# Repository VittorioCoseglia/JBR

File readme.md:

# JBR 

**JBR** es un parlante amplificado estéreo de diseño abierto. Combina dos etapas de potencia **clase AB** de 12 W sobre 8 Ω, una fuente lineal simétrica y un receptor **Bluetooth 5.0** (módulo [VHM‑314](docs/datasheet/VHM-314.pdf)), todo dentro de un gabinete impreso en 3D.

El repositorio reúne el diseño completo en **KiCad 9**, los planos de fabricación, el modelo 3D del gabinete, la simulación en **[Multisim](docs/markdown/simulation.md)** y el manual de usuario. Está pensado como proyecto educativo y como base reutilizable para otros amplificadores.

> [!WARNING]
> El equipo funciona con **220 V AC**. El interior del gabinete tiene tensiones peligrosas: no lo abras ni lo manipules conectado a la red. Las reparaciones y el primer encendido deben realizarse por un técnico.

## Contenido

- [Características](#características)
- [Arquitectura](#arquitectura)
- [Placas](#placas)
- [Estructura del repositorio](#estructura-del-repositorio)
- [Puesta en marcha](#puesta-en-marcha)
- [Fabricación](#fabricación)
- [Seguridad](#seguridad)
- [Créditos y contacto](#créditos-y-contacto)

## Características

| Característica | Valor |
|---|---|
| Configuración | Estéreo, 2 canales (2 placas AB) |
| Potencia | **2 × 12 W RMS @ 8 Ω**|
| Rieles de alimentación | ≈ ±16 VDC nominales (transformador 12‑0‑12 VAC) |
| Alimentación | 220 V AC, 50/60 Hz |
| Bluetooth | 5.0, módulo **[VHM‑314](docs/datasheet/VHM-314.pdf)** |
| Gabinete | 270 × 140 × 135 mm |
| Herramientas | KiCad 9.0, SolidWorks 2022, AutoCAD, Multisim 14 |

## Arquitectura

```mermaid
flowchart LR
    AC["220 V AC"] --> PSU["±12 V AC<br/>Fuente ±16 VDC"]
    PSU -->|"+VDC / GND / -VDC"| AMP_L["AB<br/>canal izquierdo"]
    PSU -->|"+VDC / GND / -VDC"| AMP_R["AB<br/>canal derecho"]
    PSU -->|"VCC / GND"| BT["VHM-314<br/>Bluetooth 5.0"]
    BT -->|"audio L"| AMP_L
    BT -->|"audio R"| AMP_R
    AMP_L --> SPK_L["Parlante 8 Ω"]
    AMP_R --> SPK_R["Parlante 8 Ω"]
```

La fuente entrega tres salidas ±VDC: dos se usan para las etapas de potencia y una para el control. El módulo Bluetooth entrega las señales de audio izquierda y derecha a cada amplificador.

## Placas

| Placa | Función | Documentación | Esquemático |
|---|---|---|---|
| **AB** | Etapa de potencia clase AB, 12 W / 8 Ω (una por canal) | [AB](docs/markdown/ab.md) | [ABSchem](docs/PDF/Schem/ABSchem.pdf) |
| **Fuente x4** | Fuente simétrica ±16 VDC con tres salidas | [Fuente](docs/markdown/fuente.md) | [FuenteSchem](docs/PDF/Schem/FuenteSchem.pdf) |
| **Control** | Regulador 5 V, LED y conexión del módulo Bluetooth | [Control](docs/markdown/control.md) | [ControlSchem](docs/PDF/Schem/ControlSchem.pdf) |

También están disponibles las [transferencias para fabricación](docs/PDF/Transferencia), los [datasheets](docs/datasheet) y la [lista de materiales](docs/BOM.xlsx). El esquemático del amplificador está en [ABSchem](docs/PDF/Schem/ABSchem.pdf).

## Estructura del repositorio

```text
.
├── AB/                    # Proyecto KiCad de la etapa de potencia
├── Control/                  # Proyecto KiCad del control y Bluetooth
├── Fuente/                   # Proyecto KiCad de la fuente simétrica
├── gabinete/                 # Ensamble SolidWorks, STL para impresión 3D y STEP
├── Manual/                   # Manual de usuario en Word, fotos y video
├── Simulacion/               # Simulación del amplificador en Multisim
├── docs/
│   ├── BOM.xlsx              # Lista de materiales completa
│   ├── datasheet/            # Hojas de datos de los componentes principales
│   ├── img/                  # Fotos e imágenes de las placas y del equipo
│   ├── PDF/                  # Esquemáticos (Schem/) y transferencias por placa
│   └── markdown/             # Documentación técnica de cada placa
└── readme.md
```

## Puesta en marcha

1. **Revisar la fuente antes de conectar las placas.** Con el transformador conectado y sin carga, medir ±VDC entre cada riel y GND. Verificar también que no haya tensión AC en las salidas.
2. **Ajustar el bias de cada AB** con el amplificador sin señal y con la placa a temperatura de trabajo. Medir la caída sobre `R8` y `R9` (0,33 Ω) y ajustar `RV2` hasta obtener aproximadamente **10–15 mV** en cada resistencia (≈ 30–45 mA por par de salida). Ver [AB](docs/markdown/ab.md#ajustes).
3. **Ajustar la ganancia** con `RV1` (100 kΩ). Para una entrada típica de 1 V RMS, un valor cercano a 12 kΩ entrega la ganancia necesaria para la potencia nominal.
4. **Conectar el control** a una salida de la fuente y verificar los 5 V en la salida del [L7805](docs/datasheet/L7805.pdf) antes de colocar el módulo [VHM‑314](docs/datasheet/VHM-314.pdf).
5. **Vincular el Bluetooth**: encender el equipo y buscar el dispositivo **HFW-BT** desde el celular.

## Fabricación

- **Placas:** 100 × 50 mm, 2 capas, componentes de agujero pasante (THT). Los PDF de transferencia están en [`docs/PDF/Transferencia/`](docs/PDF/Transferencia).
- **Componentes:** la [BOM](docs/BOM.xlsx) está separada por placa ([fuente](docs/markdown/fuente.md), [AB](docs/markdown/ab.md), [control](docs/markdown/control.md), [gabinete](docs/markdown/case.md) y [accesorios](docs/markdown/case.md)). La BOM del AB corresponde a **un canal**; para el equipo estéreo hay que duplicarla.
- **Disipadores:** los [TIP31C](docs/datasheet/TIP31C.pdf)/[TIP32C](docs/datasheet/TIP32C.pdf) van sobre disipador TO‑220 y los [BD139](docs/datasheet/BD13X.pdf)/[BD140](docs/datasheet/BD13X.pdf) sobre disipador TO‑126. Usar grasa térmica y aislantes si el disipador queda unido al chasis.
- **[gabinete](docs/markdown/case.md):** piezas `abajo.STL` y `arriba.STL` en `gabinete/Impresion 3D/stl/` para impresión 3D, más el ensamble SolidWorks y las piezas STEP de las placas.
## Seguridad

- Conectar únicamente a **220 V AC, 50/60 Hz** con el cable C13 incluido.
- No abrir el gabinete con el equipo conectado. Los capacitores de la fuente pueden quedar cargados después de apagarlo: descargarlos con una resistencia antes de manipular.
- No cubrir el equipo ni apoyarlo sobre superficies blandas; los disipadores y el transformador se calientan.
- Evitar el uso prolongado a volumen máximo o con sonido distorsionado.
- Mantener lejos del agua y fuera del alcance de los niños.
- Reemplazar el fusible solo por otro del mismo tipo y valor, con el equipo **desconectado de la red**.

## Créditos y contacto

- **Autor:** Vittorio Coseglia
- **Repositorio:** [github.com/VittorioCoseglia/JBR](https://github.com/VittorioCoseglia/JBR)
- **Consultas y errores:** [abrir un issue](https://github.com/VittorioCoseglia/JBR/issues)
- **Correo:** vittorio.coseglia@gmail.com

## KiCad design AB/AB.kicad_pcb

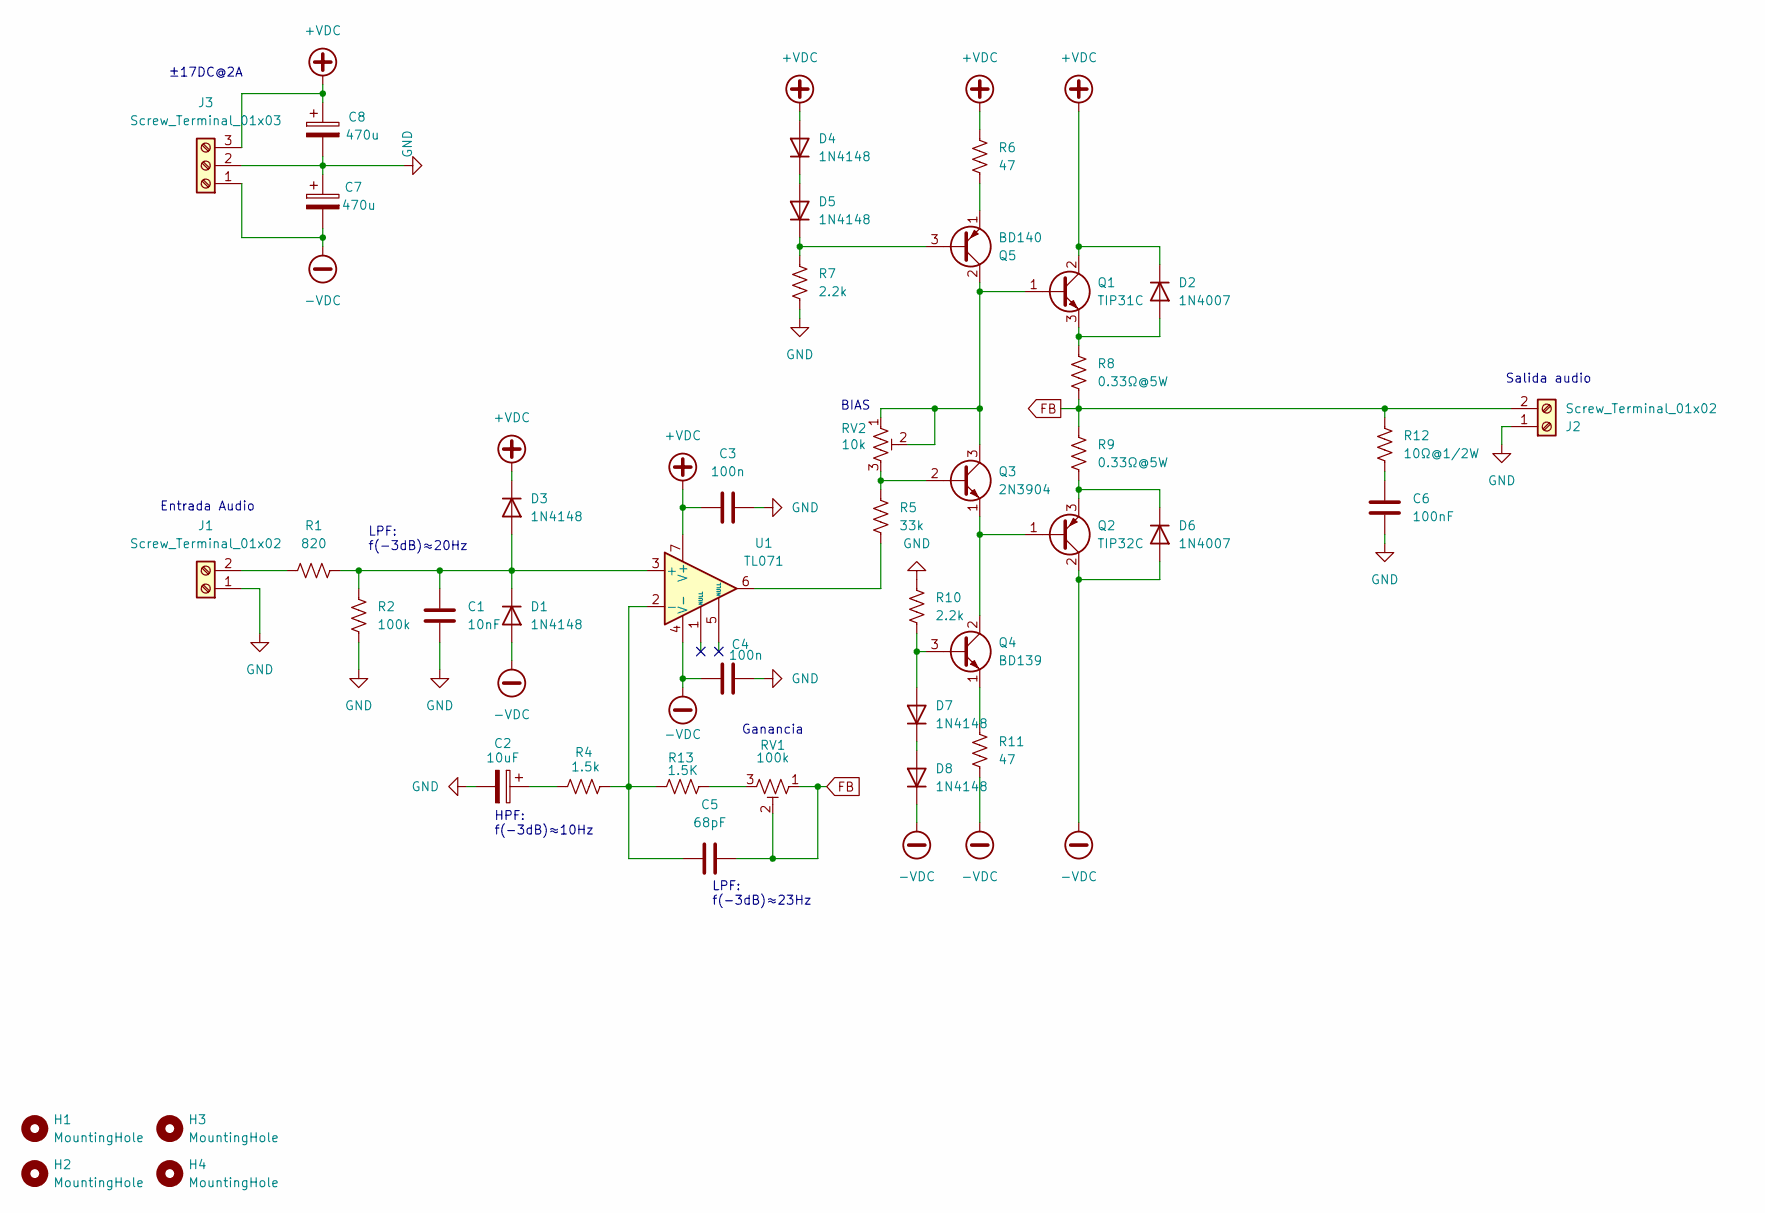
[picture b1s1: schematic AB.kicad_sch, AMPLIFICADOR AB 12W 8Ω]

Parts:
C1: 10nF; C_Disc_D5.0mm_W2.5mm_P2.50mm
C2: 10uF; C_Radial_D6.3mm_H11.0mm_P2.50mm
C3, C4: 100n; C_Disc_D5.0mm_W2.5mm_P2.50mm
C5: 68pF; C_Disc_D3.0mm_W2.0mm_P2.50mm
C6: 100nF; C_Disc_D5.0mm_W2.5mm_P2.50mm
C7, C8: 470u; C_Radial_D10.0mm_H20.0mm_P5.00mm
D1, D3, D4, D5, D7, D8: 1N4148; D_DO-35_SOD27_P7.62mm_Horizontal
D2, D6: 1N4007; D_DO-41_SOD81_P10.16mm_Horizontal
H1, H2, H3, H4: MountingHole; MountingHole_3.2mm_M3
J1, J2: Screw_Terminal_01x02; TerminalBlock_Phoenix_MKDS-1,5-2_1x02_P5.00mm_Horizontal
J3: Screw_Terminal_01x03; TerminalBlock_Phoenix_MKDS-1,5-3_1x03_P5.00mm_Horizontal
Q1: TIP31C; TO-220-3_Vertical
Q2: TIP32C; TO-220-3_Vertical
Q3: 2N3904; TO-92_Inline
Q4: BD139; TO-126-3_Vertical
Q5: BD140; TO-126-3_Vertical
R1: 820; R_Axial_DIN0207_L6.3mm_D2.5mm_P10.16mm_Horizontal
R2: 100k; R_Axial_DIN0207_L6.3mm_D2.5mm_P10.16mm_Horizontal
R4: 1.5k; R_Axial_DIN0207_L6.3mm_D2.5mm_P10.16mm_Horizontal
R5: 33k; R_Axial_DIN0207_L6.3mm_D2.5mm_P10.16mm_Horizontal
R6, R11: 47; R_Axial_DIN0207_L6.3mm_D2.5mm_P10.16mm_Horizontal
R7, R10: 2.2k; R_Axial_DIN0207_L6.3mm_D2.5mm_P10.16mm_Horizontal
R8, R9: 0.33Ω@5W; R_Axial_Power_L25.0mm_W6.4mm_P30.48mm
R12: 10Ω@1/2W; R_Axial_DIN0309_L9.0mm_D3.2mm_P15.24mm_Horizontal
R13: 1.5K; R_Axial_DIN0207_L6.3mm_D2.5mm_P10.16mm_Horizontal
RV1: 100k; Potentiometer_Bourns_3296W_Vertical
RV2: 10k; Potentiometer_Bourns_3296W_Vertical
U1: TL071; DIP-8_W7.62mm

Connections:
+VDC: C3.2, C8.1, D2.1 (K), D3.1 (K), D4.2 (A), J3.3, Q1.2 (C), R6.1, U1.7 (V+)
-VDC: C4.2, C7.2, D1.2 (A), D6.2 (A), D8.1 (K), J3.1, Q2.2 (C), R11.2, U1.4 (V-)
FB: C5.1, J2.2, R8.2, R9.1, R12.1, RV1.1, RV1.2
GND: C1.2, C2.2, C3.1, C4.1, C6.2, C7.1, C8.2, J1.1, J2.1, J3.2, R2.2, R7.2, R10.1
unnamed: C2.1, R4.1
unnamed: C6.1, R12.2
unnamed: C1.1, D1.1 (K), D3.2 (A), R1.2, R2.1, U1.3 (+)
unnamed: D2.2 (A), Q1.3 (E), R8.1
unnamed: D4.1 (K), D5.2 (A)
unnamed: D5.1 (K), Q5.3 (B), R7.1
unnamed: D6.1 (K), Q2.3 (E), R9.2
unnamed: D7.2 (A), Q4.3 (B), R10.2
unnamed: D7.1 (K), D8.2 (A)
unnamed: J1.2, R1.1
unnamed: Q1.1 (B), Q3.3 (C), Q5.2 (C), RV2.1, RV2.2
unnamed: Q2.1 (B), Q3.1 (E), Q4.2 (C)
unnamed: Q3.2 (B), R5.1, RV2.3
unnamed: Q4.1 (E), R11.1
unnamed: Q5.1 (E), R6.2
unnamed: R5.2, U1.6
unnamed: R13.2, RV1.3
unnamed: C5.2, R4.2, R13.1, U1.2 (-)

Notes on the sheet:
LPF: f(-3dB)≈23Hz
Ganancia
Entrada Audio
±17DC@2A
LPF: f(-3dB)≈20Hz
BIAS
HPF: f(-3dB)≈10Hz
Salida audio

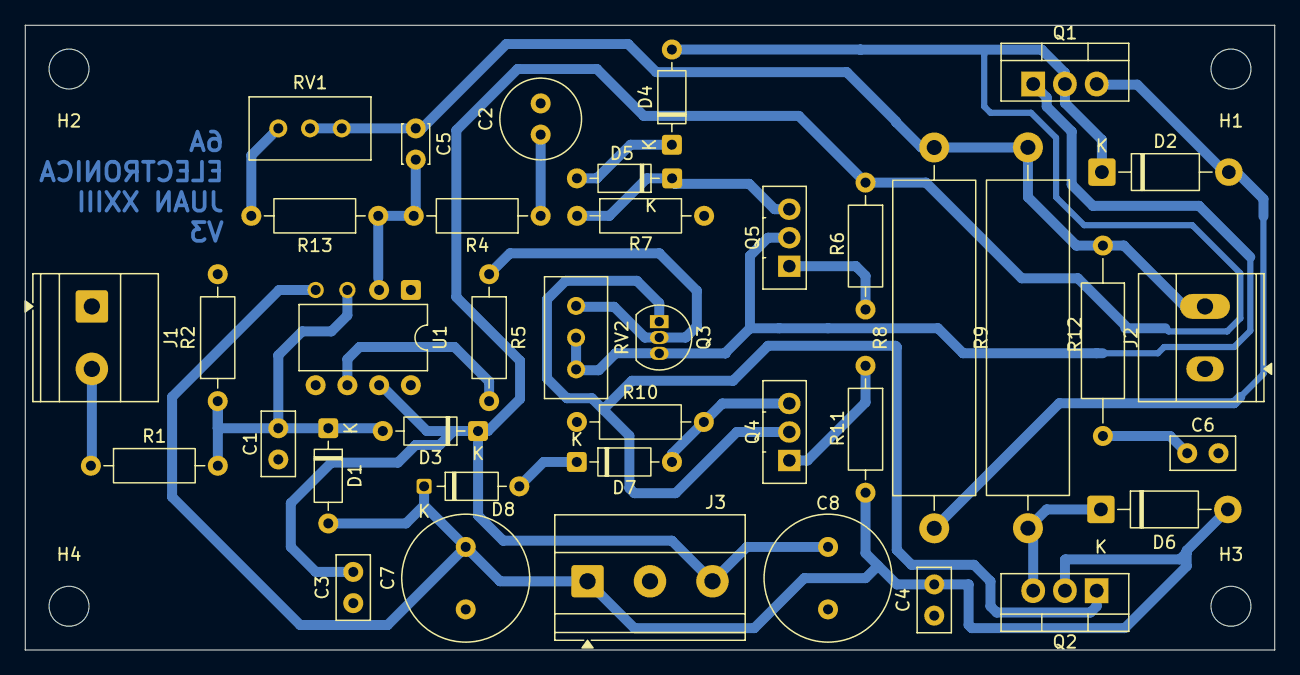
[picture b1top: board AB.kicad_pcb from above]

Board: 2 copper layers, 100.0 x 50.0 mm, 43 parts (0 on the bottom side), 22 nets.

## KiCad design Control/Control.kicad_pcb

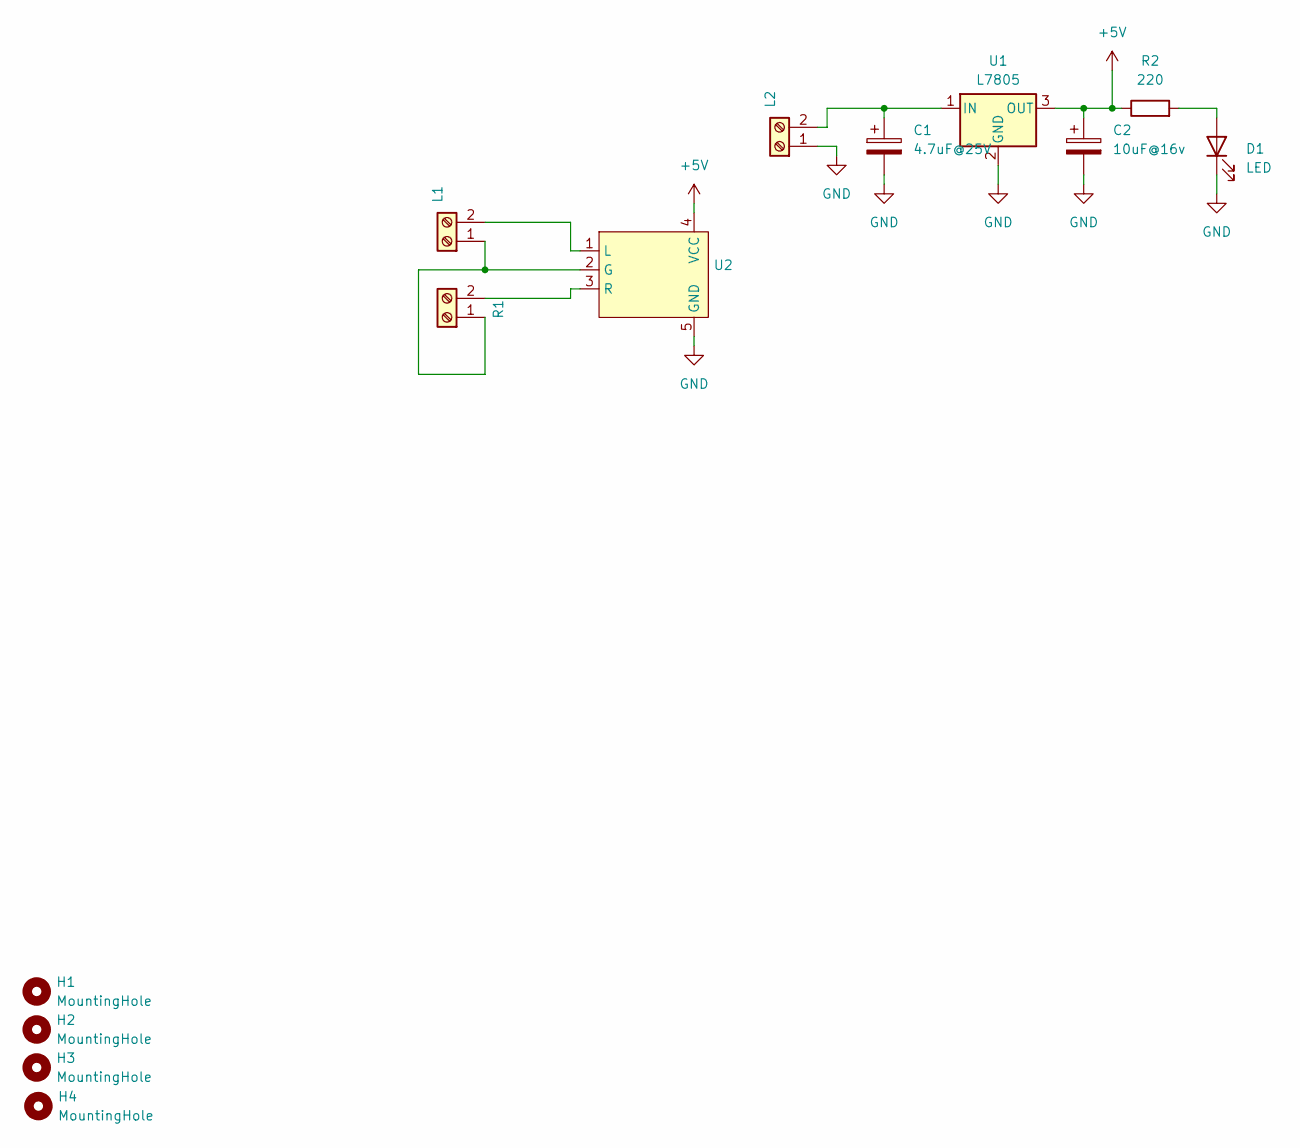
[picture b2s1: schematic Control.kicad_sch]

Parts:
C1: 4.7uF@25V; C_Radial_D5.0mm_H11.0mm_P2.00mm
C2: 10uF@16v; C_Radial_D5.0mm_H11.0mm_P2.00mm
D1: LED; LED_D5.0mm
H1, H2, H3, H4: MountingHole; MountingHole_3.2mm_M3
L1, L2: Screw_Terminal_01x02; TerminalBlock_Phoenix_MKDS-1,5-2_1x02_P5.00mm_Horizontal
R1: Screw_Terminal_01x02; TerminalBlock_Phoenix_MKDS-1,5-2_1x02_P5.00mm_Horizontal
R2: 220; R_Axial_DIN0207_L6.3mm_D2.5mm_P10.16mm_Horizontal
U1: L7805; TO-220-3_Horizontal_TabDown
U2: VHM-314

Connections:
+5V: C2.1, R2.1, U1.3 (OUT), U2.4 (VCC)
GND: C1.2, C2.2, D1.1 (K), L2.1, U1.2 (GND), U2.5 (GND)
unnamed: D1.2 (A), R2.2
unnamed: L1.1, R1.1, U2.2 (G)
unnamed: L1.2, U2.1 (L)
unnamed: C1.1, L2.2, U1.1 (IN)
unnamed: R1.2, U2.3 (R)

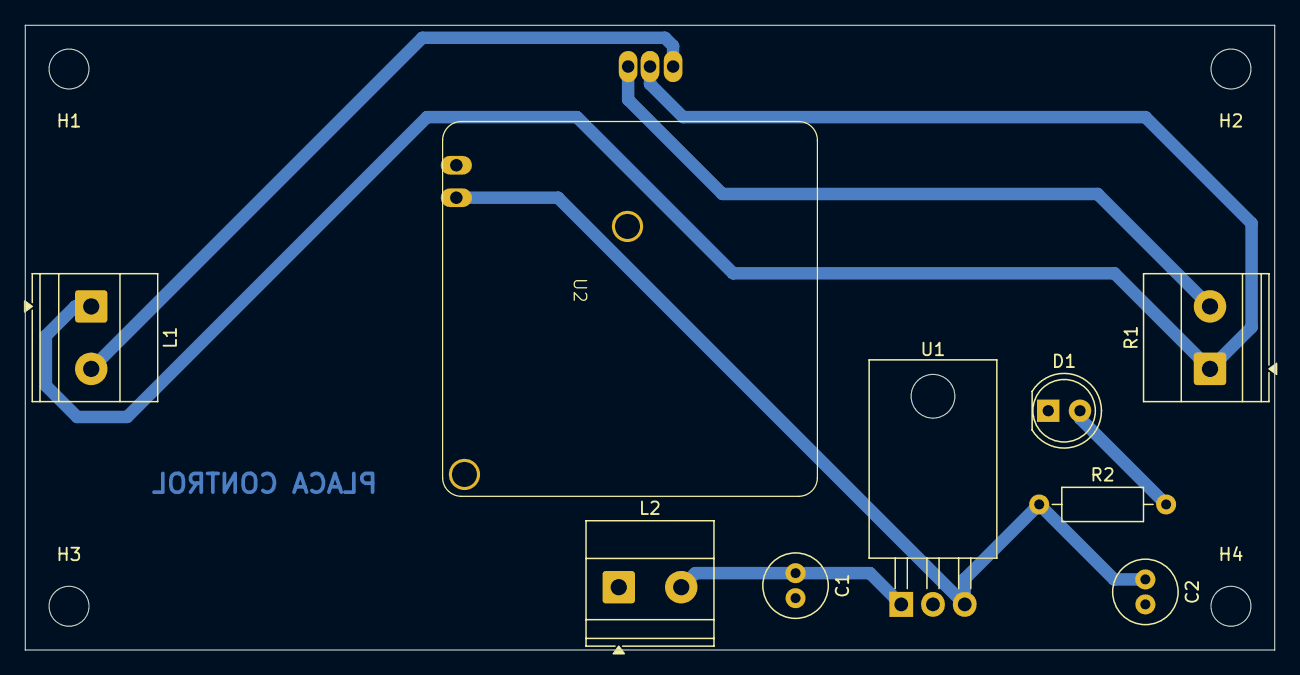
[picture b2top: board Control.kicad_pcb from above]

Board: 2 copper layers, 100.0 x 50.0 mm, 13 parts (0 on the bottom side), 7 nets.

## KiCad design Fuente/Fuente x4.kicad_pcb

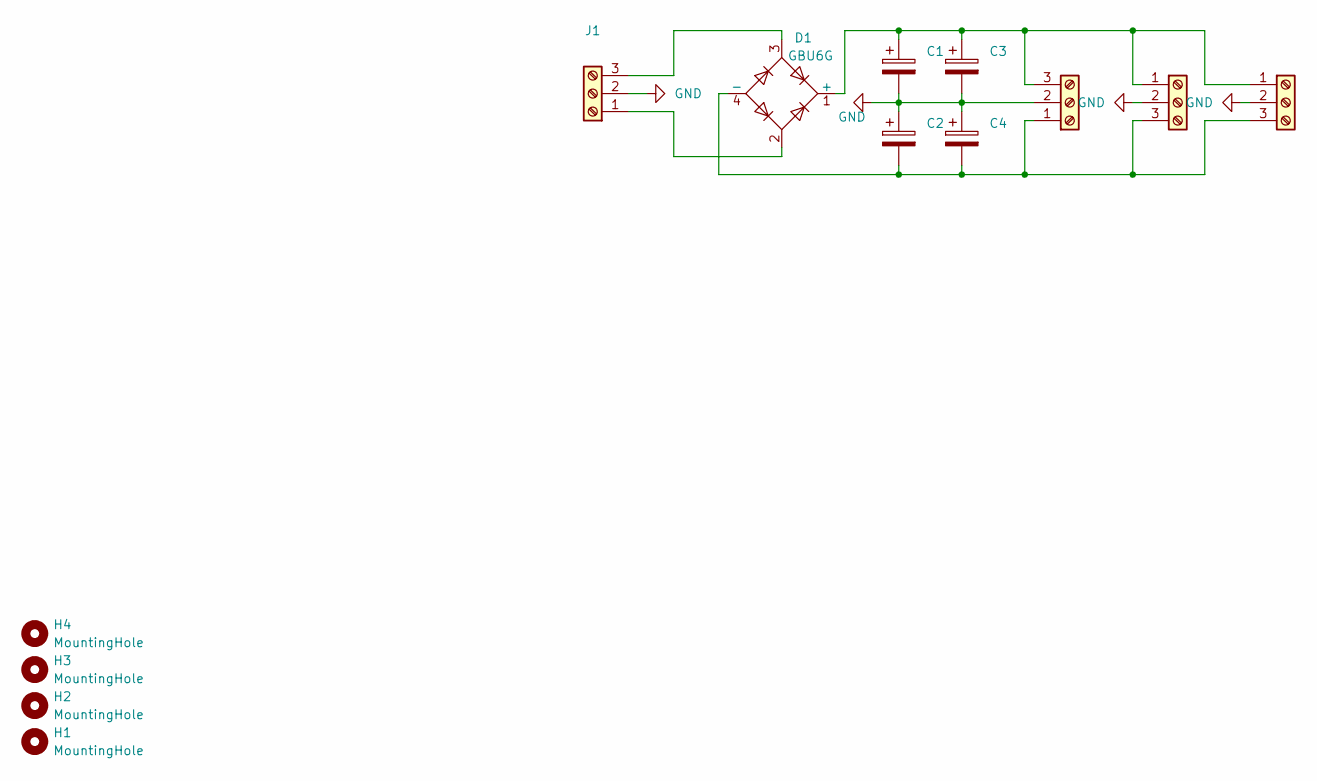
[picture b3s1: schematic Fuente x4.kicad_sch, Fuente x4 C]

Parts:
C1, C2, C3, C4: C_Polarized; CP_Radial_D22.0mm_P10.00mm_SnapIn
D1: GBU6G; Diode_Bridge_Vishay_GBU
H1, H2, H3, H4: MountingHole; MountingHole_3.2mm_M3
J1, J2, J3, J4: Screw_Terminal_01x03; TerminalBlock_Phoenix_MKDS-1,5-3_1x03_P5.00mm_Horizontal

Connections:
GND: C1.2, C2.1, C3.2, C4.1, J1.2, J2.2, J3.2, J4.2
unnamed: C1.1, C3.1, D1.1 (+), J2.3, J3.1, J4.1
unnamed: C2.2, C4.2, D1.4 (-), J2.1, J3.3, J4.3
unnamed: D1.2, J1.1
unnamed: D1.3, J1.3

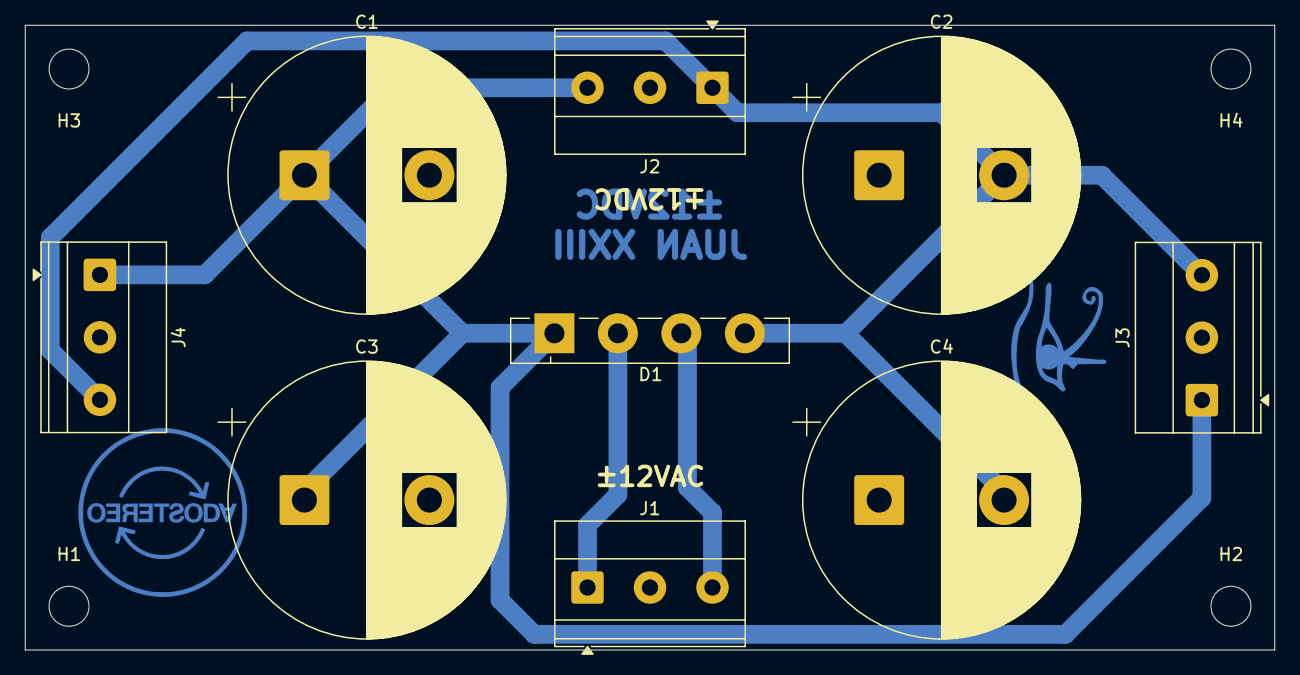
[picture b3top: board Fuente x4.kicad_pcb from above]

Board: 2 copper layers, 100.0 x 50.0 mm, 13 parts (0 on the bottom side), 5 nets.
